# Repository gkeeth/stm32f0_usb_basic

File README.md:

# stm32f0_usb_basic
Basic development board for STM32F042K6Tx (USB line)

No frills, basic dev board for STM32F0 USB line. Has a user button, two user LEDs, all GPIOs broken out, and not much else.

Unless otherwise noted, all hardware is licensed under a [Creative Commons Attribution-ShareAlike 4.0 International License][cc-by-sa] and all software is licensed under the [LGPLv3][lgpl].

[![CC BY-SA 4.0][cc-by-sa-image]][cc-by-sa]
[![License: LGPL v3][lgpl-image]][lgpl]

[cc-by-sa]: http://creativecommons.org/licenses/by-sa/4.0/
[cc-by-sa-image]: https://licensebuttons.net/l/by-sa/4.0/88x31.png
[lgpl]: https://www.gnu.org/licenses/lgpl-3.0
[lgpl-image]: https://img.shields.io/badge/License-LGPLv3-blue.svg

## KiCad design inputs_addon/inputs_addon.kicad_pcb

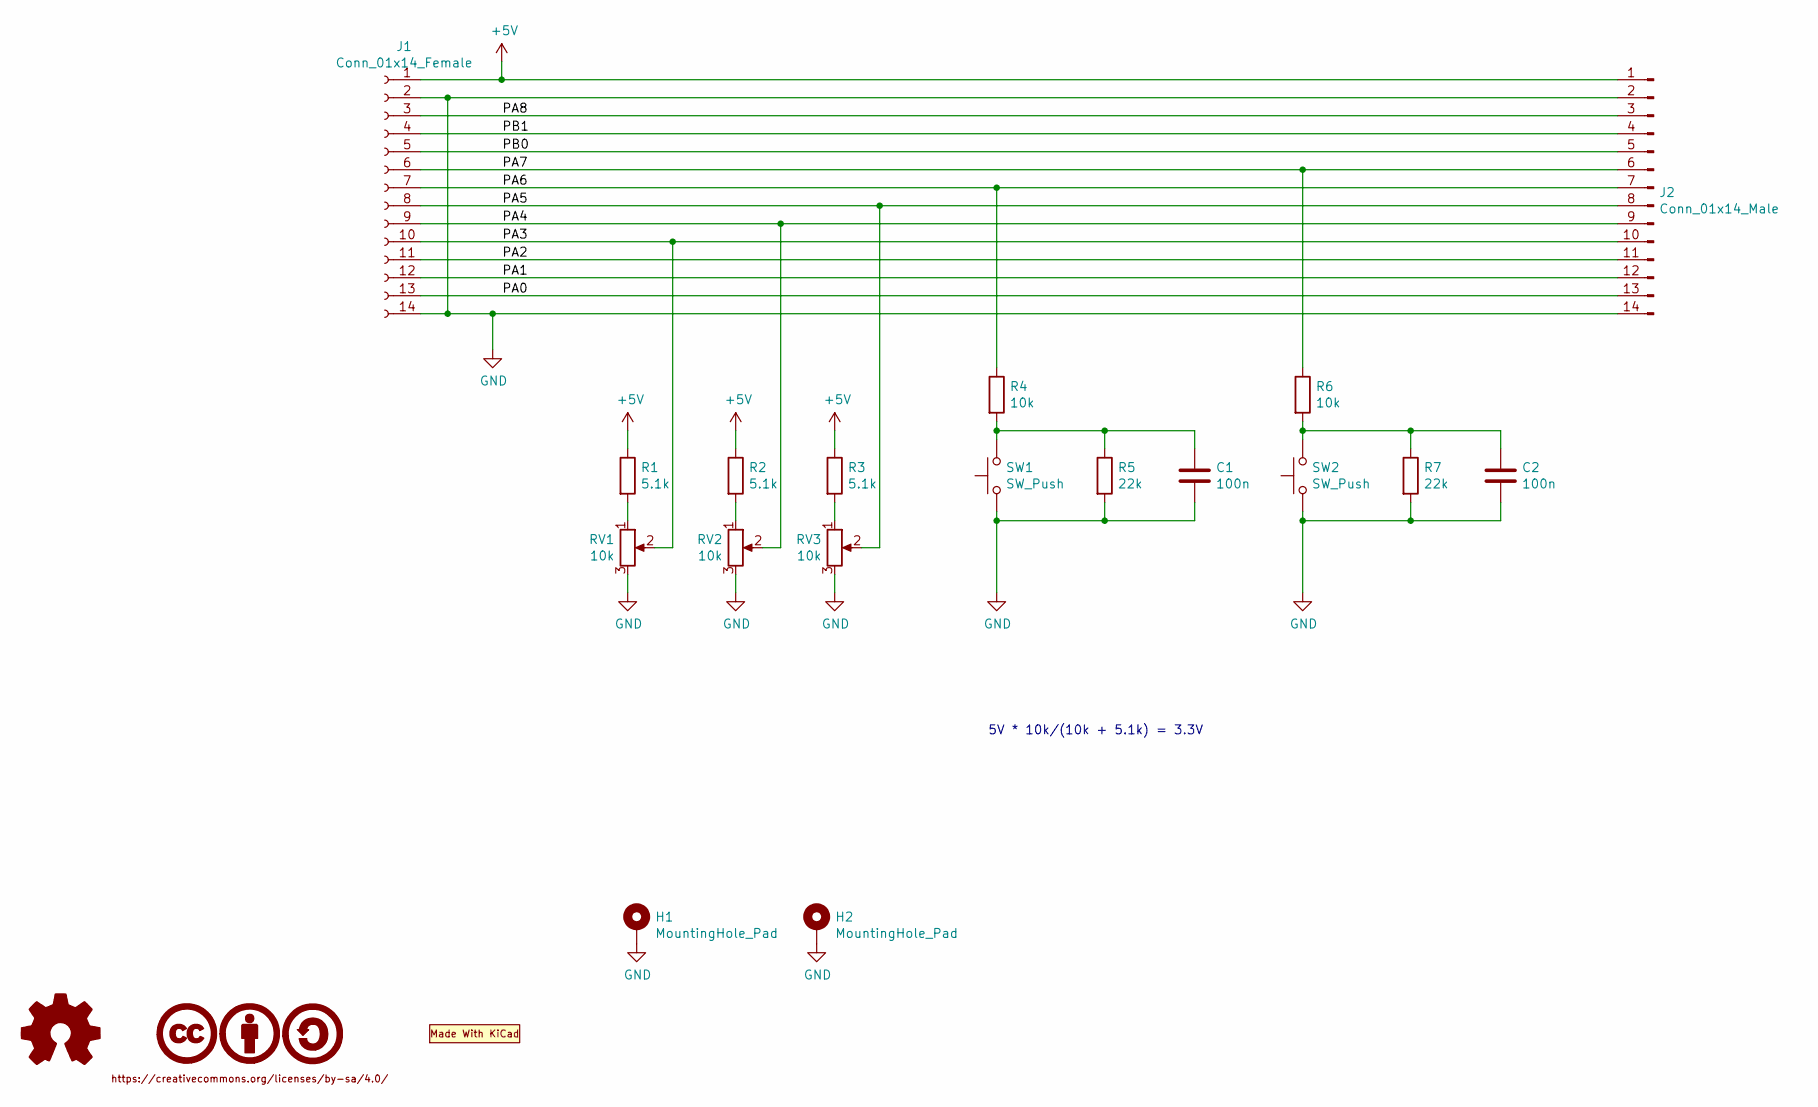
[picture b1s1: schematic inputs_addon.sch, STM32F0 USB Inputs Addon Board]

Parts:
C1, C2: 100n; C_0603_1608Metric
H1, H2: MountingHole_Pad; MountingHole_3.2mm_M3_Pad
J1: Conn_01x14_Female; PinSocket_1x14_P2.54mm_Vertical
J2: Conn_01x14_Male; PinHeader_1x14_P2.54mm_Vertical
LOGO1: Logo_Open_Hardware_Small; OSHW-Logo_5.7x6mm_SilkScreen
LOGO2: CC-BY-SA_0.33in; CC-BY-SA_SilkScreenTop_Small
LOGO3: Logo_MadeWithKiCad; KiCad-Logo2_5mm_SilkScreen
R1, R2, R3: 5.1k; R_0603_1608Metric
R4, R6: 10k; R_0603_1608Metric
R5, R7: 22k; R_0603_1608Metric
RV1, RV2, RV3: 10k; Potentiometer_Bourns_PTV09A-1_Single_Vertical; Manufacturer PN PTV09A-4020F-B103‎
SW1, SW2: SW_Push; SW_SPST_B3S-1000

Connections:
+5V: J1.1, J2.1, R1.1, R2.1, R3.1
/PA0: J1.13, J2.13
/PA1: J1.12, J2.12
/PA2: J1.11, J2.11
/PA3: J1.10, J2.10, RV1.2
/PA4: J1.9, J2.9, RV2.2
/PA5: J1.8, J2.8, RV3.2
/PA6: J1.7, J2.7, R4.1
/PA7: J1.6, J2.6, R6.1
/PA8: J1.3, J2.3
/PB0: J1.5, J2.5
/PB1: J1.4, J2.4
GND: C1.2, C2.2, H1.1, H2.1, J1.2, J1.14, J2.2, J2.14, R5.2, R7.2, RV1.3, RV2.3, RV3.3, SW1.1, SW2.1
unnamed: C1.1, R4.2, R5.1, SW1.2
unnamed: C2.1, R6.2, R7.1, SW2.2
unnamed: R1.2, RV1.1
unnamed: R2.2, RV2.1
unnamed: R3.2, RV3.1

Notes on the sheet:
5V * 10k/(10k + 5.1k) = 3.3V

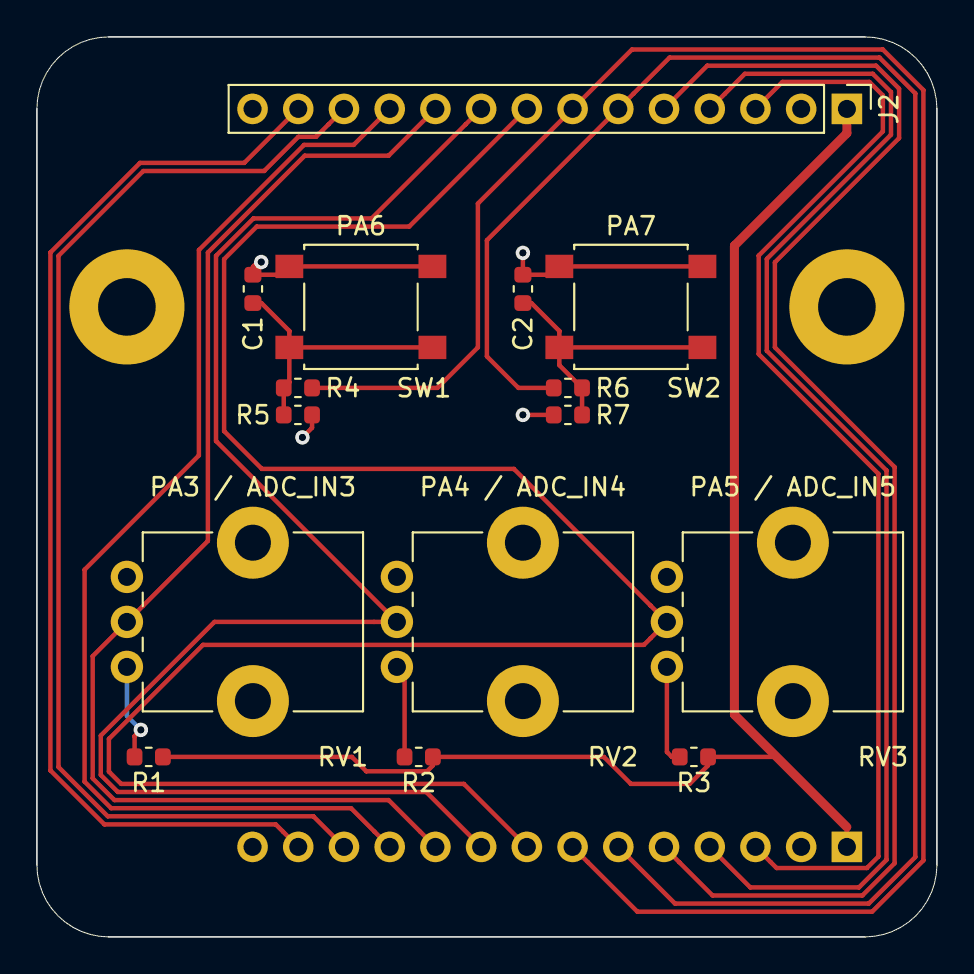
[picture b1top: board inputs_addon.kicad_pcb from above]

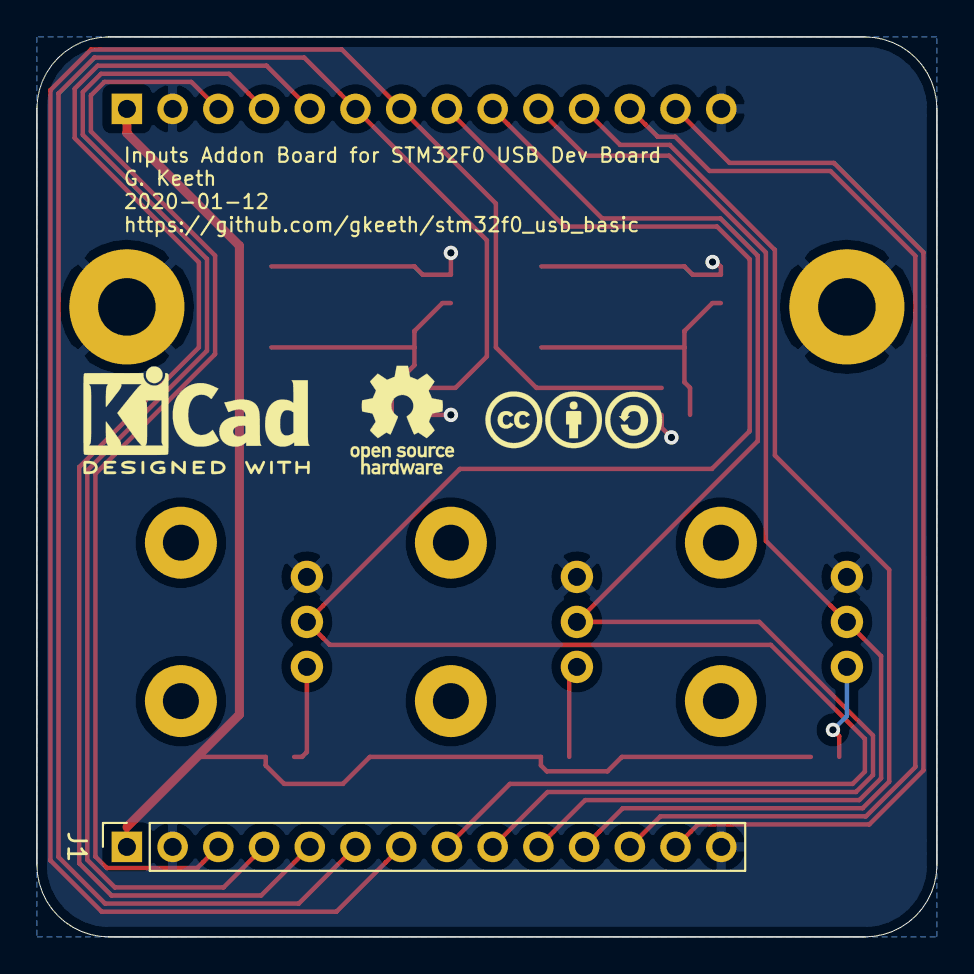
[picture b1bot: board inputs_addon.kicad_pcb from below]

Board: 2 copper layers, 50.0 x 50.0 mm, 21 parts (4 on the bottom side), 18 nets.

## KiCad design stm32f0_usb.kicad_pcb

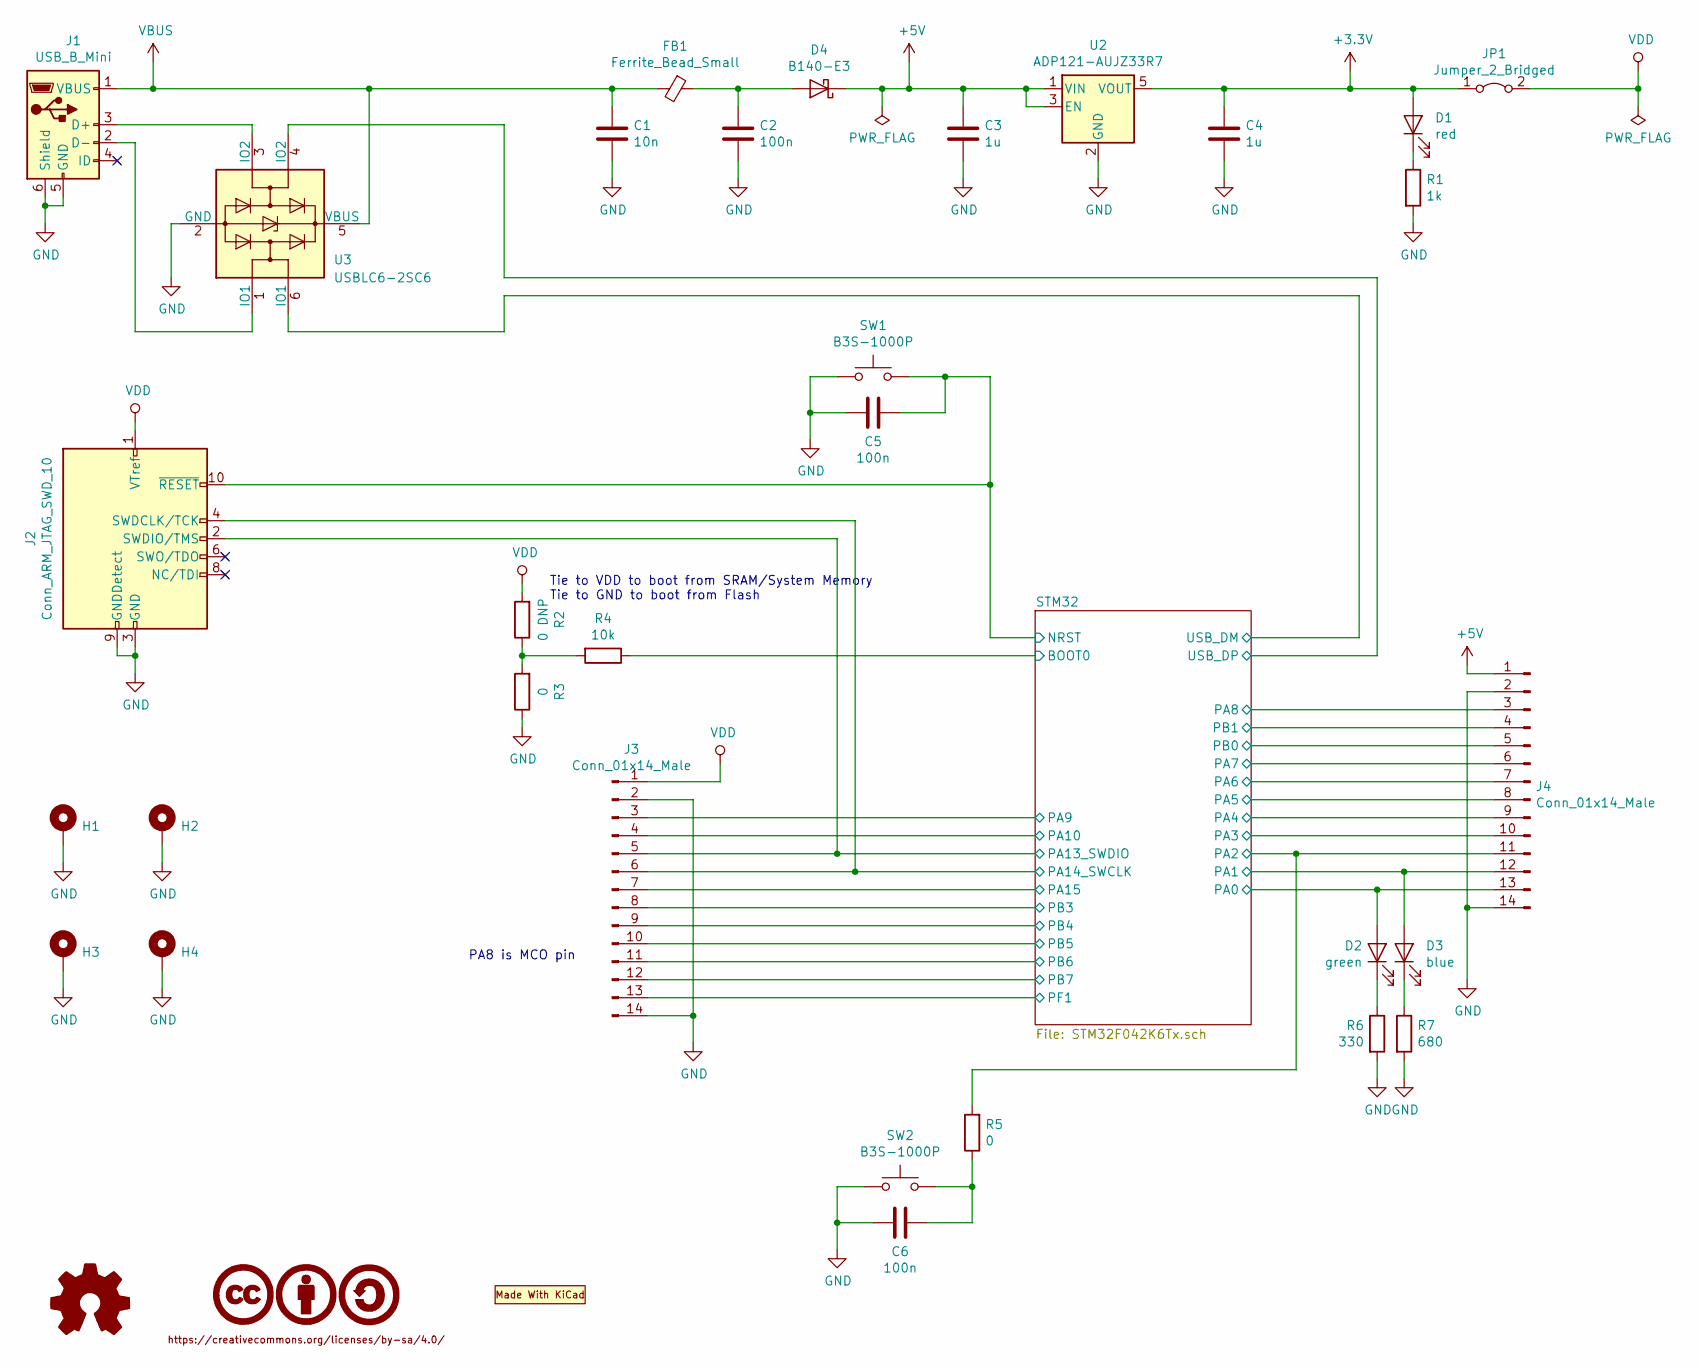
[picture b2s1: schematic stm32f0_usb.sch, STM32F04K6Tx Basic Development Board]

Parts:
C1: 10n; C_0603_1608Metric
C2, C5, C6: 100n; C_0603_1608Metric
C3, C4: 1u; C_0805_2012Metric
D1: red; LED_0603_1608Metric_Castellated
D2: green; LED_0603_1608Metric_Castellated
D3: blue; LED_0603_1608Metric_Castellated
D4: B140-E3; D_SMA
FB1: Ferrite_Bead_Small; L_0603_1608Metric
H1, H2, H3, H4: MountingHole_Pad; MountingHole_3.2mm_M3_Pad
J1: USB_B_Mini; USB_Mini-B_Wuerth_65100516121_Horizontal
J2: Conn_ARM_JTAG_SWD_10; PinHeader_2x05_P1.27mm_Vertical_SMD
J3, J4: Conn_01x14_Male; PinHeader_1x14_P2.54mm_Vertical
JP1: Jumper_2_Bridged; PinHeader_1x02_P2.54mm_Vertical
LOGO1: Logo_MadeWithKiCad; KiCad-Logo2_5mm_SilkScreen
LOGO2: CC-BY-SA_0.33in; CC-BY-SA_SilkScreenTop_Small
LOGO3: Logo_Open_Hardware_Small; OSHW-Symbol_6.7x6mm_SilkScreen
R1: 1k; R_0603_1608Metric
R2: 0 DNP; R_0603_1608Metric
R3, R5: 0; R_0603_1608Metric
R4: 10k; R_0603_1608Metric
R6: 330; R_0603_1608Metric
R7: 680; R_0603_1608Metric
SW1, SW2: B3S-1000P; SW_SPST_B3S-1000
U2: ADP121-AUJZ33R7; TSOT-23-5
U3: USBLC6-2SC6; SOT-23-6

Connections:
+3V3: C4.1, D1.2 (A), JP1.1 (A), U2.5 (VOUT)
+5V: C3.1, D4.1 (K), J4.1, U2.1 (VIN), U2.3 (EN)
/STM32/BOOT0: R4.1; also elsewhere on the board
/STM32/NRST: C5.1, J2.10 (~RESET~), SW1.2; also elsewhere on the board
/STM32/PA0: D2.2 (A), J4.13; also elsewhere on the board
/STM32/PA1: D3.2 (A), J4.12; also elsewhere on the board
/STM32/PA2: J4.11, R5.2; also elsewhere on the board
/STM32/PA3: J4.10; also elsewhere on the board
/STM32/PA4: J4.9; also elsewhere on the board
/STM32/PA5: J4.8; also elsewhere on the board
/STM32/PA6: J4.7; also elsewhere on the board
/STM32/PA7: J4.6; also elsewhere on the board
/STM32/PA8: J4.3; also elsewhere on the board
/STM32/PA9: J3.3; also elsewhere on the board
/STM32/PA10: J3.4; also elsewhere on the board
/STM32/PA13_SWDIO: J2.2 (SWDIO/TMS), J3.5; also elsewhere on the board
/STM32/PA14_SWCLK: J2.4 (SWDCLK/TCK), J3.6; also elsewhere on the board
/STM32/PA15: J3.7; also elsewhere on the board
/STM32/PB0: J4.5; also elsewhere on the board
/STM32/PB1: J4.4; also elsewhere on the board
/STM32/PB3: J3.8; also elsewhere on the board
/STM32/PB4: J3.9; also elsewhere on the board
/STM32/PB5: J3.10; also elsewhere on the board
/STM32/PB6: J3.11; also elsewhere on the board
/STM32/PB7: J3.12; also elsewhere on the board
/STM32/PF1: J3.13; also elsewhere on the board
/STM32/USB_DM: U3.6 (IO1); also elsewhere on the board
/STM32/USB_DP: U3.4 (IO2); also elsewhere on the board
GND: C1.2, C2.2, C3.2, C4.2, C5.2, C6.2, H1.1, H2.1, H3.1, H4.1, J1.5 (GND), J1.6 (Shield), J2.3 (GND), J2.5 (GND), J2.9 (GNDDetect), J3.2, J3.14, J4.2, J4.14, R1.2, R3.1, R6.2, R7.2, SW1.1, SW2.1, U2.2 (GND), U3.2 (GND); also elsewhere on the board
unnamed: C2.1, D4.2 (A), FB1.1
unnamed: C6.1, R5.1, SW2.2
unnamed: D1.1 (K), R1.1
unnamed: D2.1 (K), R6.1
unnamed: D3.1 (K), R7.1
unnamed: J1.2 (D-), U3.1 (IO1)
unnamed: J1.3 (D+), U3.3 (IO2)
unnamed: R2.1, R3.2, R4.2
VBUS: C1.1, FB1.2, J1.1 (VBUS), U3.5 (VBUS)
VDD: J2.1 (VTref), J3.1, JP1.2 (B), R2.2; also elsewhere on the board

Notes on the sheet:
PA8 is MCO pin
Tie to VDD to boot from SRAM/System Memory Tie to GND to boot from Flash

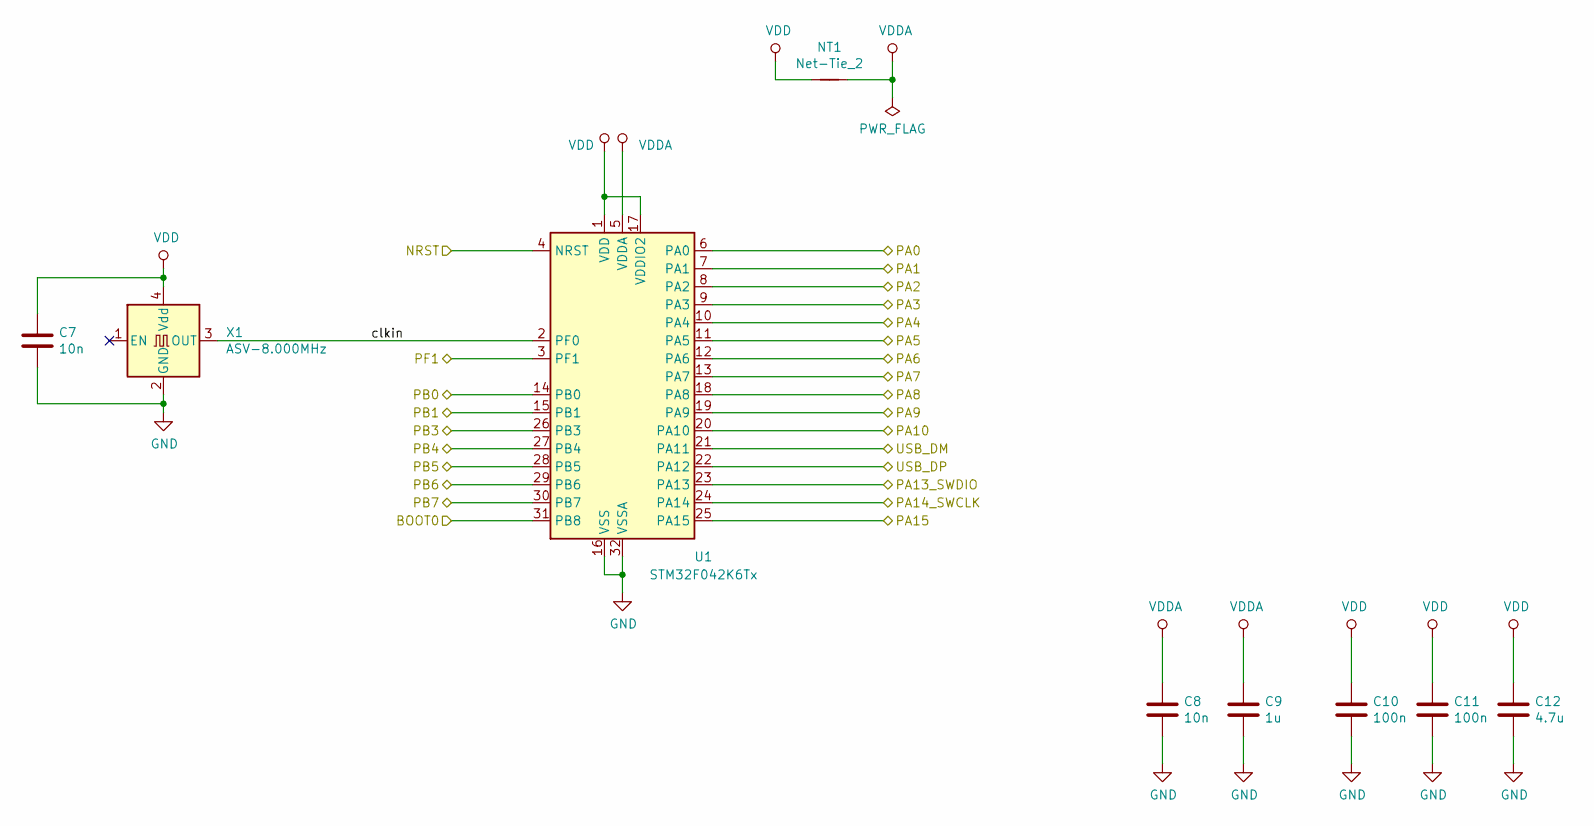
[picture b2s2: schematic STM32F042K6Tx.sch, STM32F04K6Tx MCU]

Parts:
C7, C8: 10n; C_0603_1608Metric
C9: 1u; C_0805_2012Metric
C10, C11: 100n; C_0603_1608Metric
C12: 4.7u; C_0805_2012Metric
NT1: Net-Tie_2; NetTie-2_SMD_Pad0.5mm
U1: STM32F042K6Tx; LQFP-32_7x7mm_P0.8mm
X1: ASV-8.000MHz; Oscillator_SMD_Abracon_ASV-4Pin_7.0x5.1mm

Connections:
/STM32/BOOT0: U1.31 (PB8); also elsewhere on the board
/STM32/NRST: U1.4 (NRST); also elsewhere on the board
/STM32/PA0: U1.6 (PA0); also elsewhere on the board
/STM32/PA1: U1.7 (PA1); also elsewhere on the board
/STM32/PA2: U1.8 (PA2); also elsewhere on the board
/STM32/PA3: U1.9 (PA3); also elsewhere on the board
/STM32/PA4: U1.10 (PA4); also elsewhere on the board
/STM32/PA5: U1.11 (PA5); also elsewhere on the board
/STM32/PA6: U1.12 (PA6); also elsewhere on the board
/STM32/PA7: U1.13 (PA7); also elsewhere on the board
/STM32/PA8: U1.18 (PA8); also elsewhere on the board
/STM32/PA9: U1.19 (PA9); also elsewhere on the board
/STM32/PA10: U1.20 (PA10); also elsewhere on the board
/STM32/PA13_SWDIO: U1.23 (PA13); also elsewhere on the board
/STM32/PA14_SWCLK: U1.24 (PA14); also elsewhere on the board
/STM32/PA15: U1.25 (PA15); also elsewhere on the board
/STM32/PB0: U1.14 (PB0); also elsewhere on the board
/STM32/PB1: U1.15 (PB1); also elsewhere on the board
/STM32/PB3: U1.26 (PB3); also elsewhere on the board
/STM32/PB4: U1.27 (PB4); also elsewhere on the board
/STM32/PB5: U1.28 (PB5); also elsewhere on the board
/STM32/PB6: U1.29 (PB6); also elsewhere on the board
/STM32/PB7: U1.30 (PB7); also elsewhere on the board
/STM32/PF1: U1.3 (PF1); also elsewhere on the board
/STM32/USB_DM: U1.21 (PA11); also elsewhere on the board
/STM32/USB_DP: U1.22 (PA12); also elsewhere on the board
/STM32/clkin: U1.2 (PF0), X1.3 (OUT)
GND: C7.2, C8.2, C9.2, C10.2, C11.2, C12.2, U1.16 (VSS), U1.32 (VSSA), X1.2 (GND); also elsewhere on the board
VDD: C7.1, C10.1, C11.1, C12.1, NT1.1, U1.1 (VDD), U1.17 (VDDIO2), X1.4 (Vdd); also elsewhere on the board
VDDA: C8.1, C9.1, NT1.2, U1.5 (VDDA)

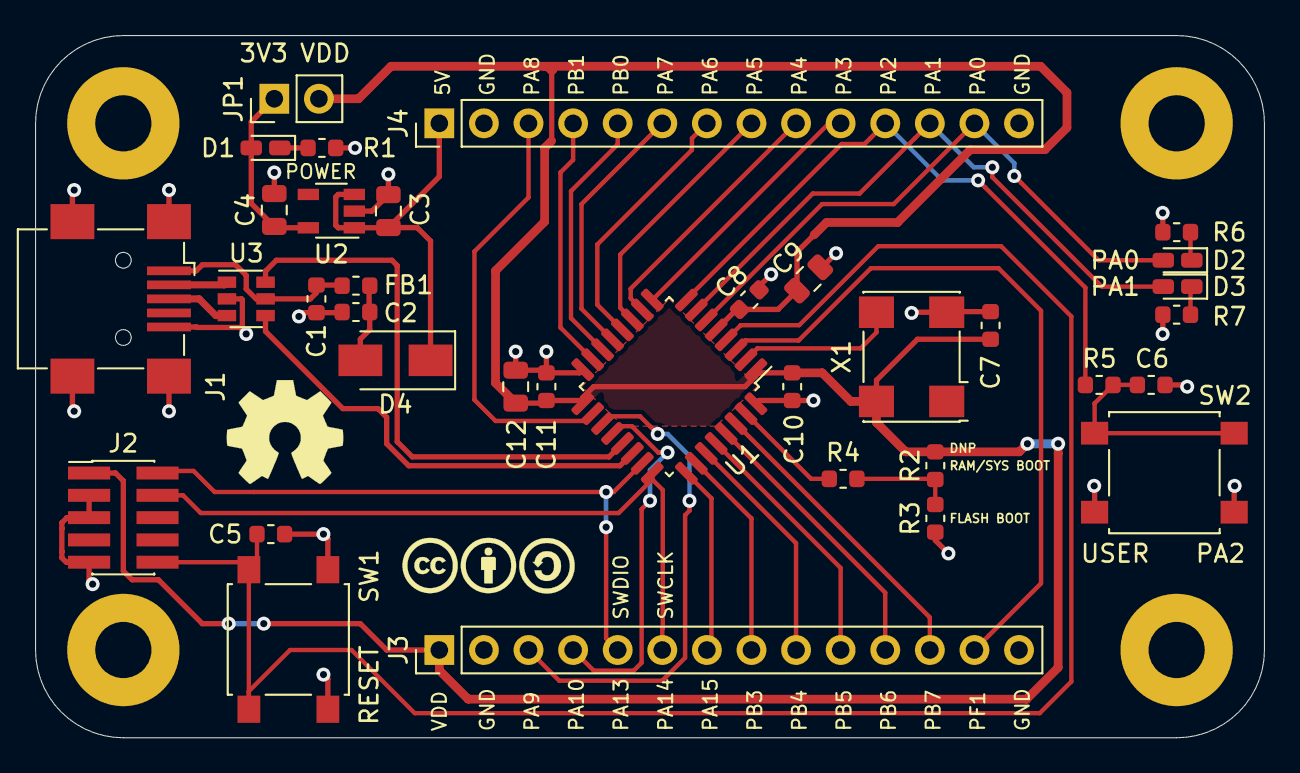
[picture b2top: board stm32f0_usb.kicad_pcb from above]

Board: 2 copper layers, 70.0 x 40.0 mm, 43 parts (1 on the bottom side), 41 nets.

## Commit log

2020-01-10 initial commit. Full initial schematic for board.
2020-01-10 add gitignore
2020-01-10 remove irrelevant ignores
2020-01-10 don't ignore -cache.lib and rescue libs
2020-01-11 initial board setup and rough placement
2020-01-11 label clkin net
2020-01-11 update GPIO/header pinout to ease routing
2020-01-11 update usb esd connections
2020-01-11 initial routing mostly finished
2020-01-12 complete routing
2020-01-12 fatten power traces, add pinout table, neaten silk
2020-01-12 add inputs addon board, fully routed
2020-01-14 switch to vertical headers, add mounting holes
2020-01-14 add dimensions to dwgs.user layer
2020-01-14 plot outputs for r0
2020-01-14 plot gerbers for inputs_addon r0
2020-01-14 refill zones
2020-01-14 update readme with license and board images
2020-01-14 add CC-BY-SA license
2020-01-22 add blink example
2020-01-22 update gitignore to ignore gcc compiler/linker outputs
2020-05-17 add GPL license statement to readme for software
2020-05-17 add readme for src/
2020-05-17 add GPL badge to readme
2020-05-17 add GPL link
2020-05-17 add license header to blink example
2020-05-17 update license header
2020-05-17 add license header
2020-05-17 add blink2 example
2020-05-17 remove redundant blink2 example
2020-05-17 add basic usb example
2020-05-17 functional usbcdc example
2020-05-17 let driver automatically calculate wTotalLength
2020-05-17 fix typo
2020-05-17 correct READMEs to specify LGPL rather than GPL (oops)
2020-05-17 clean up comments
2020-05-17 fix typo in README
